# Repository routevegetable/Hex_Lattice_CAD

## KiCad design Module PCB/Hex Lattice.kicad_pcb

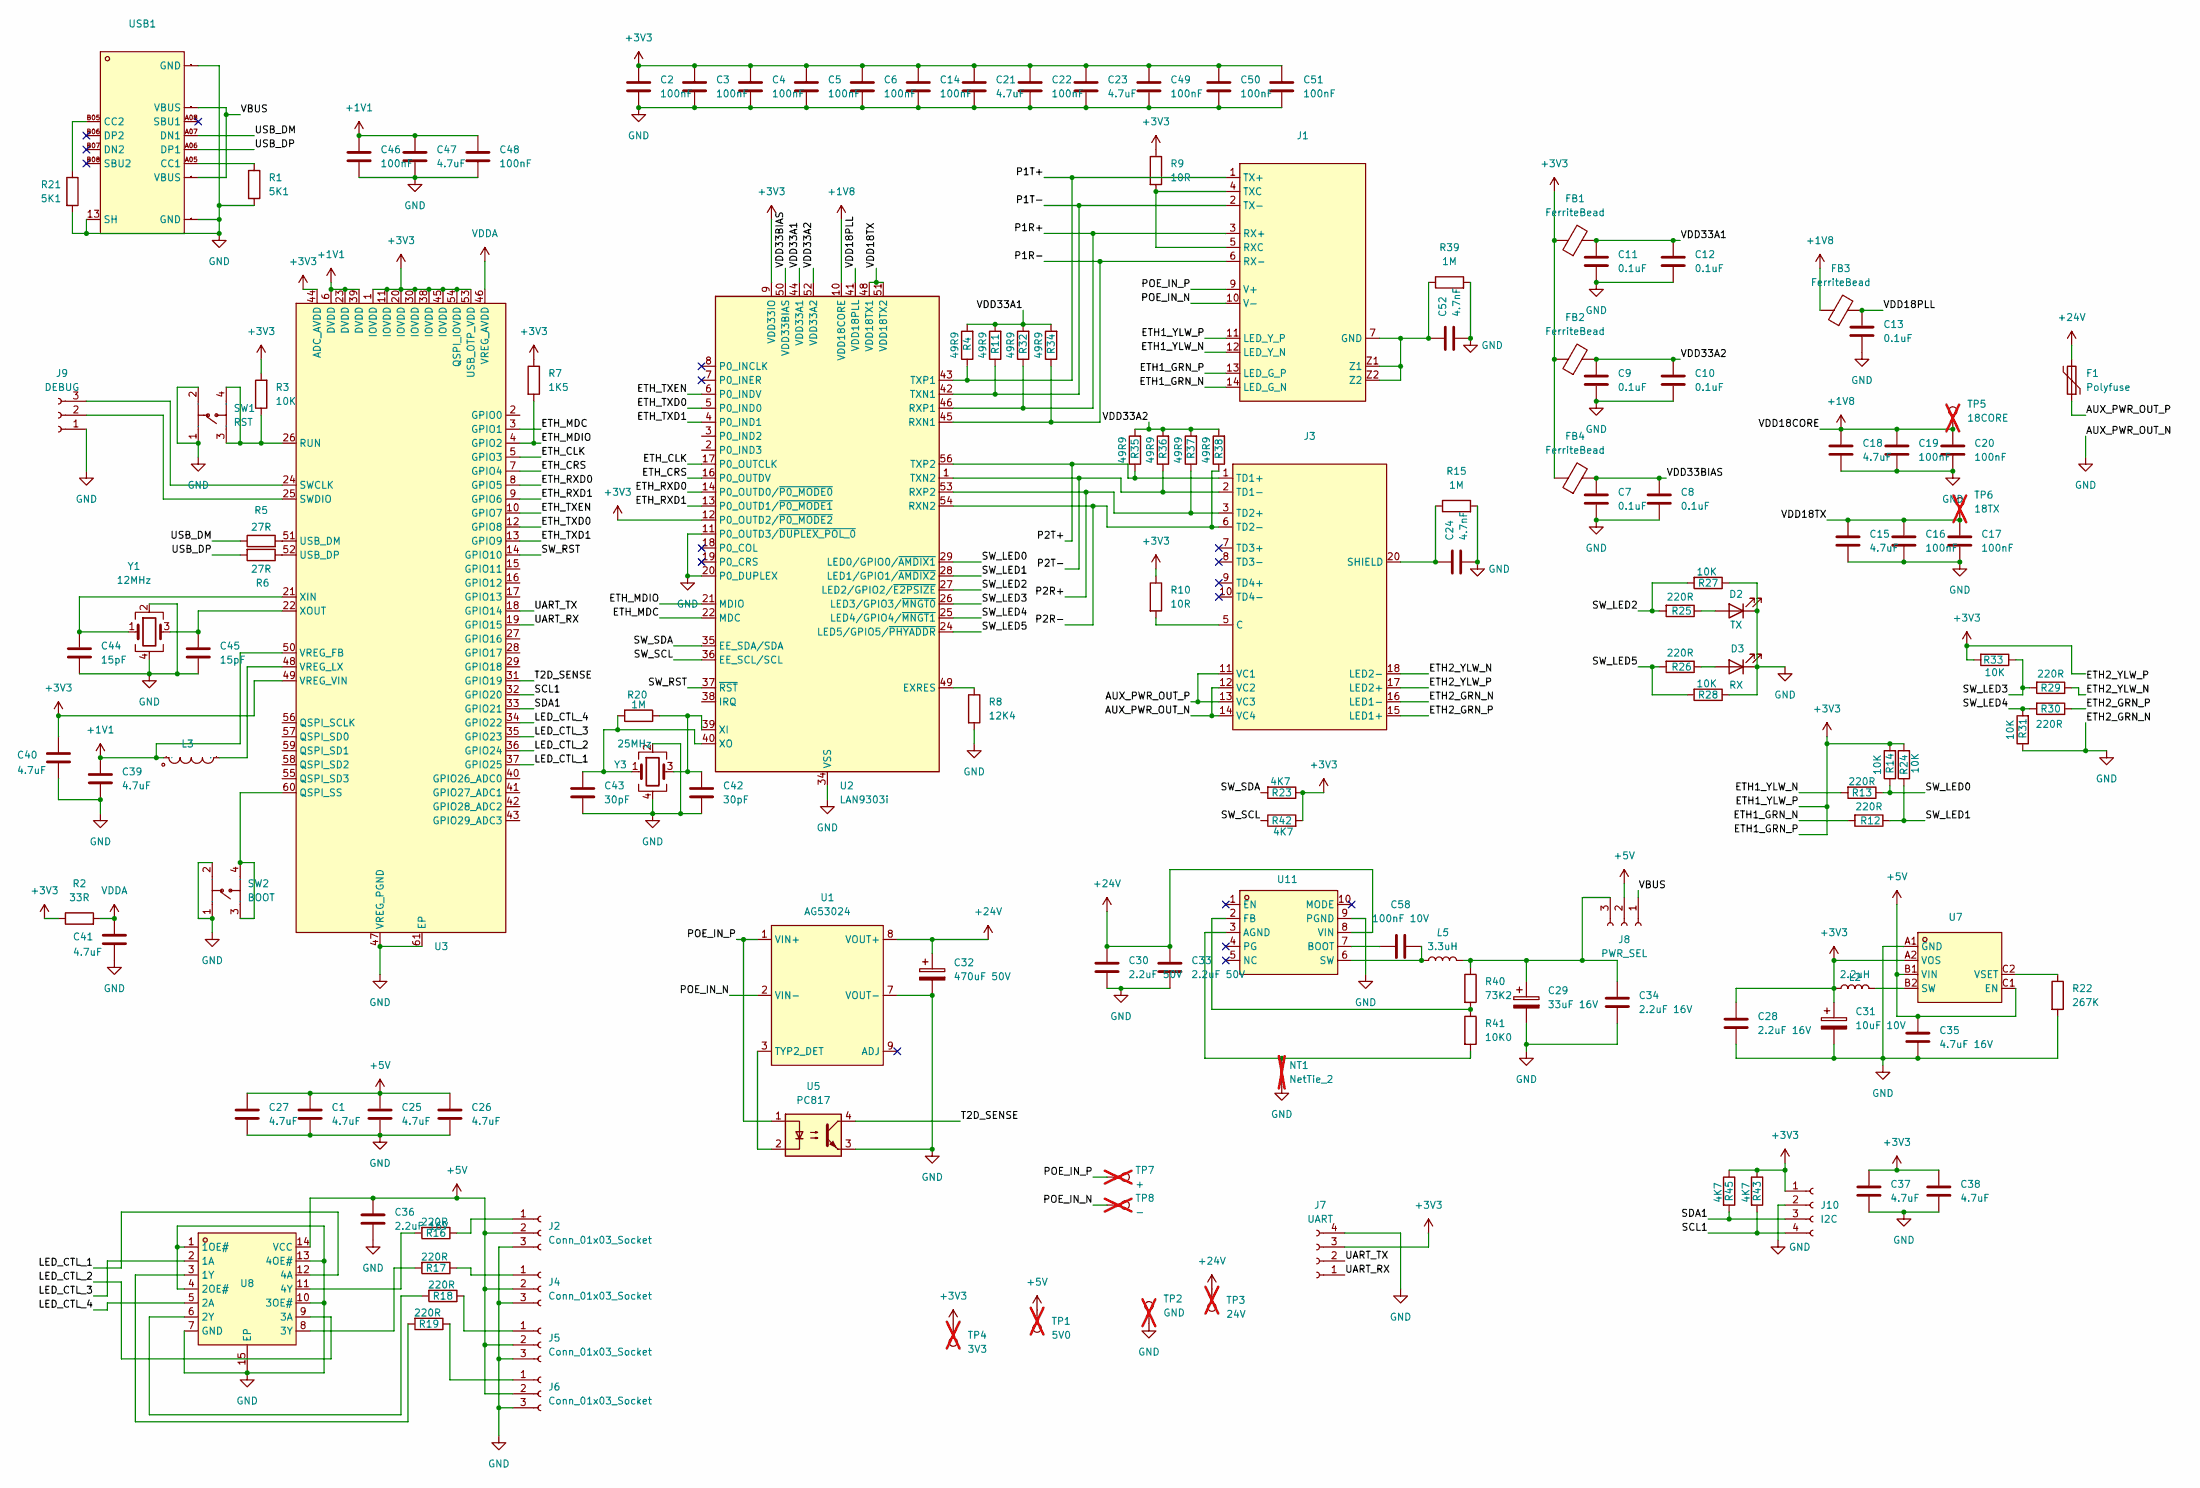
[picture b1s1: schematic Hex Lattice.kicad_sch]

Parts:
C1, C25, C26, C27, C37, C38: 4.7uF; C_0805_2012Metric; LCSC C380343
C2, C3, C4, C5, C6, C14, C16, C17, C19, C20, C22, C46, C48, C49, C50, C51: 100nF; C_0201_0603Metric; LCSC C6119757
C7, C8, C9, C10, C11, C12, C13: 0.1uF; C_0201_0603Metric; LCSC C6119757
C15, C18, C21, C23, C39, C40, C41: 4.7uF; C_0603_1608Metric; LCSC C7419427
C24, C52: 4.7nF; C_1206_3216Metric; LCSC C784438
C28, C34, C36: 2.2uF 16V; C_0805_2012Metric; LCSC C167029
C29: 33uF 16V; CP_Elec_5x5.4; LCSC C970668
C30, C33: 2.2uF 50V; C_0805_2012Metric; LCSC C2903667
C31: 10uF 10V; CP_Elec_4x5.8; LCSC C401860
C32: 470uF 50V; CP_Elec_10x12.5; LCSC C22469994
C35: 4.7uF 16V; C_0805_2012Metric; LCSC C22399641
C42, C43: 30pF; C_0201_0603Metric; LCSC C5142545
C44, C45: 15pF; C_0201_0603Metric; LCSC C22374851
C47: 4.7uF; C_0402_1005Metric; LCSC C33595851
C58: 100nF 10V; C_0201_0603Metric; LCSC C6119757
D2: TX; LED_0402_1005Metric; LCSC C74338
D3: RX; LED_0402_1005Metric; LCSC C74338
F1: Polyfuse; Fuse_Bourns_MF-RG300; LCSC C2680602
FB1, FB2, FB3, FB4: FerriteBead; L_0603_1608Metric; LCSC C3032643
J1: RJ45-TH_ARJP11A-MASA-B-A-EMU2; Manufacturer Part HR861153C; LCSC C19724782
J2, J4, J5, J6: Conn_01x03_Socket; PinHeader_1x03_P2.54mm_Vertical; LCSC C429954
J3: RJ45-TH_DGUK111Q334AB2A2DP057; Manufacturer Part DGUK111Q334AB2A2DP057; LCSC C19725175
J7: UART; CONN-TH_ZH-4A; LCSC C722937
J8: PWR_SEL; PinHeader_1x03_P2.54mm_Vertical; LCSC C429954
J9: DEBUG; PinHeader_1x03_P2.54mm_Vertical; LCSC C2937625
J10: I2C; CONN-SMD_4P-P1.00_ZX-SH1.0-4PLN; LCSC C7430453
L2: 2.2uH; L0806; LCSC C337893
L3: 3.3uH; IND-SMD_L2.0-W1.6_AOTA-B201610S3R3-101-T; Manufacturer Part AOTA-B201610S3R3-101-T; LCSC C42411119
L5: 3.3uH; L_Murata_LQH55DN_5.7x5.0mm; LCSC C48579566
NT1: NetTie_2; NetTie-2_SMD_Pad0.5mm; not fitted
R1, R21: 5K1; R_0402_1005Metric; LCSC C49652827
R2: 33R; R_0201_0603Metric; LCSC C49654095
R3, R14, R24, R27, R28, R31, R33: 10K; R_0201_0603Metric; LCSC C49653975
R4, R11, R32, R34, R35, R36, R37, R38: 49R9; R_0201_0603Metric; LCSC C49653934
R5, R6: 27R; R_0201_0603Metric; LCSC C49654512
R7: 1K5; R_0201_0603Metric; LCSC C49654140
R8: 12K4; R_0402_1005Metric; LCSC C138060
R9, R10: 10R; R_0201_0603Metric; LCSC C49653825
R12, R13, R25, R26, R29, R30: 220R; R_0201_0603Metric; LCSC C49654383
R15, R39: 1M; R_0402_1005Metric; LCSC C49652954
R16, R17, R18, R19: 220R; R_0402_1005Metric; LCSC C49653096
R20: 1M; R_0201_0603Metric; LCSC C49654212
R22: 267K; R_0402_1005Metric; LCSC C49254102
R23, R42, R43, R45: 4K7; R_0201_0603Metric; LCSC C49654757
R40: 73K2; R_0402_1005Metric; LCSC C50669973
R41: 10K0; R_0402_1005Metric; LCSC C52677569
SW1: RST; SW-SMD_4P-L5.2-W5.2-P3.70-LS6.4; Manufacturer Part TS1187A16015; LCSC C22375382
SW2: BOOT; SW-SMD_4P-L5.2-W5.2-P3.70-LS6.4; Manufacturer Part TS1187A16015; LCSC C22375382
TP1: 5V0; TestPoint_Pad_D3.0mm; not fitted
TP2: GND; TestPoint_Pad_D3.0mm; not fitted
TP3: 24V; TestPoint_Pad_D3.0mm; not fitted
TP4: 3V3; TestPoint_Pad_D3.0mm; not fitted
TP5: 18CORE; TestPoint_Pad_D2.0mm; not fitted
TP6: 18TX; TestPoint_Pad_D2.0mm; not fitted
TP7: +; TestPoint_Pad_D3.0mm; not fitted
TP8: -; TestPoint_Pad_D3.0mm; not fitted
U1: AG53024; AG53000
U2: LAN9303i; QFN-56-1EP_8x8mm_P0.5mm_EP5.9x5.9mm_ThermalVias; LCSC C633501
U3: QFN-60_L7.0-W7.0-P0.40-TL-EP3.4; Manufacturer Part RP2354A; LCSC C41378174
U5: PC817; DIP-4_W7.62mm; LCSC C52092020
U7: DSBGA-6_L1.4-W1.0-R2-C3-P0.40-BL; Manufacturer Part TPS62840YBGR; LCSC C2071139
U8: DHVQFN-14_L3.0-W2.5-P0.50-BL-EP; Manufacturer Part 74AHCT125BQ,115; LCSC C554499
U11: VQFN-HR-10_L3.0-W3.0_RPA; Manufacturer Part TPS56637RPAR; LCSC C841386
USB1: USB-C-TH_MC-110LD-L137; Manufacturer Part MC-110LDS-L150; LCSC C22374560
Y1: 12MHz; Crystal_SMD_3225-4Pin_3.2x2.5mm; LCSC C5182759
Y3: 25MHz; CRYSTAL-SMD_4P-L1.6-W1.2-BL; LCSC C51289919

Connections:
+1V1: C39.1, C46.1, C47.1, C48.1, L3.2, U3.6 (DVDD), U3.23 (DVDD), U3.39 (DVDD), U3.50 (VREG_FB)
+1V8: C18.1, C19.1, C20.1, FB3.1, TP5.1, U2.10 (VDD18CORE), U2.31 (VDD18CORE)
+3V3: C2.1, C3.1, C4.1, C5.1, C6.1, C14.1, C21.1, C22.1, C23.1, C28.2, C31.1, C37.1, C38.1, C40.1, C49.1, C50.1, C51.1, FB1.1, FB2.1, FB4.1, J1.11 (LED_Y_P), J1.13 (LED_G_P), J7.3, J10.1, L2.1, R2.1, R3.2, R7.1, R9.1, R10.1, R14.2, R23.1, R24.2, R33.2, R42.2, R43.1, R45.1, TP4.1, U2.9 (VDD33IO), U2.12 (P0_OUTD2/~P0_MODE2), U2.15 (VDD33IO), U2.23 (VDD33IO), U2.30 (VDD33IO), U2.32 (VDD33IO), U2.33 (VDD33IO), U3.1 (IOVDD), U3.11 (IOVDD), U3.20 (IOVDD), U3.30 (IOVDD), U3.38 (IOVDD), U3.44 (ADC_AVDD), U3.45 (IOVDD), U3.49 (VREG_VIN), U3.53 (USB_OTP_VDD), U3.54 (QSPI_IOVDD), U7.A2 (VOS)
+5V: C1.1, C25.1, C26.1, C27.1, C35.1, C36.2, J2.2, J4.2, J5.2, J6.2, J8.2, TP1.1, U7.B1 (VIN), U7.C1 (EN), U8.14 (VCC)
+24V: C30.2, C32.1, C33.2, F1.2, TP3.1, U1.8 (VOUT+), U11.8 (VIN)
/AUX_PWR_OUT_P: F1.1, J3.11 (VC1), J3.13 (VC3)
/ETH1_GRN_N: J1.14 (LED_G_N), R12.2
/ETH1_YLW_N: J1.12 (LED_Y_N), R13.2
/ETH2_GRN_P: J3.15 (LED1+), R30.1
/ETH2_YLW_N: J3.18 (LED2-), R29.1
/ETH2_YLW_P: J3.17 (LED2+)
/ETH_CLK: U2.17 (P0_OUTCLK), U3.5 (GPIO3)
/ETH_CRS: U2.16 (P0_OUTDV), U3.7 (GPIO4)
/ETH_MDC: U2.22 (MDC), U3.3 (GPIO1)
/ETH_MDIO: R7.2, U2.21 (MDIO), U3.4 (GPIO2)
/ETH_RXD0: U2.14 (P0_OUTD0/~P0_MODE0), U3.8 (GPIO5)
/ETH_RXD1: U2.13 (P0_OUTD1/~P0_MODE1), U3.9 (GPIO6)
/ETH_TXD0: U2.5 (P0_IND0), U3.12 (GPIO8)
/ETH_TXD1: U2.4 (P0_IND1), U3.13 (GPIO9)
/ETH_TXEN: U2.6 (P0_INDV), U3.10 (GPIO7)
/LED_CTL_1: U3.37 (GPIO25), U8.12 (4A)
/LED_CTL_2: U3.36 (GPIO24), U8.9 (3A)
/LED_CTL_3: U3.35 (GPIO23), U8.2 (1A)
/LED_CTL_4: U3.34 (GPIO22), U8.5 (2A)
/P1R+: J1.3 (RX+), R32.1, U2.46 (RXP1)
/P1R-: J1.6 (RX-), R34.1, U2.45 (RXN1)
/P1T+: J1.1 (TX+), R4.1, U2.43 (TXP1)
/P1T-: J1.2 (TX-), R11.1, U2.42 (TXN1)
/P2R+: J3.3 (TD2+), R37.1, U2.53 (RXP2)
/P2R-: J3.6 (TD2-), R38.1, U2.54 (RXN2)
/P2T+: J3.1 (TD1+), R35.1, U2.56 (TXP2)
/P2T-: J3.2 (TD1-), R36.1, U2.1 (TXN2)
/POE_IN_N: J1.10 (V-), TP8.1, U1.2 (VIN-)
/POE_IN_P: J1.9 (V+), TP7.1, U1.1 (VIN+), U5.1
/SCL1: J10.4, R43.2, U3.32 (GPIO20)
/SDA1: J10.3, R45.2, U3.33 (GPIO21)
/SW_LED0: R13.1, R14.1, U2.29 (LED0/GPIO0/~AMDIX1)
/SW_LED1: R12.1, R24.1, U2.28 (LED1/GPIO1/~AMDIX2)
/SW_LED2: R25.2, R27.2, U2.27 (LED2/GPIO2/~E2PSIZE)
/SW_LED3: R29.2, R33.1, U2.26 (LED3/GPIO3/~MNGT0)
/SW_LED4: R30.2, R31.2, U2.25 (LED4/GPIO4/~MNGT1)
/SW_LED5: R26.2, R28.2, U2.24 (LED5/GPIO5/~PHYADDR)
/SW_RST: U2.37 (~RST), U3.14 (GPIO10)
/SW_SCL: R42.1, U2.36 (EE_SCL/SCL)
/SW_SDA: R23.2, U2.35 (EE_SDA/SDA)
/T2D_SENSE: U3.31 (GPIO19), U5.4
/UART_RX: J7.1, U3.19 (GPIO15)
/UART_TX: J7.2, U3.18 (GPIO14)
/USB_DM: R5.1, USB1.A07 (DN1)
/USB_DP: R6.2, USB1.A06 (DP1)
/VBUS: J8.1, USB1.A04 (VBUS), USB1.A09 (VBUS)
/VDD18PLL: C13.1, FB3.2, U2.41 (VDD18PLL)
/VDD18TX: C15.1, C16.1, C17.1, TP6.1, U2.48 (VDD18TX1), U2.51 (VDD18TX2)
/VDD33A1: C11.1, C12.1, FB1.2, R4.2, R11.2, R32.2, R34.2, U2.44 (VDD33A1), U2.47 (VDD33A1)
/VDD33A2: C9.1, C10.1, FB2.2, R35.2, R36.2, R37.2, R38.2, U2.52 (VDD33A2), U2.55 (VDD33A2)
/VDD33BIAS: C7.1, C8.1, FB4.2, U2.50 (VDD33BIAS)
GND: C1.2, C2.2, C3.2, C4.2, C5.2, C6.2, C7.2, C8.2, C9.2, C10.2, C11.2, C12.2, C13.2, C14.2, C15.2, C16.2, C17.2, C18.2, C19.2, C20.2, C21.2, C22.2, C23.2, C24.2, C25.2, C26.2, C27.2, C28.1, C29.2, C30.1, C31.2, C32.2, C33.1, C34.1, C35.2, C36.1, C37.2, C38.2, C39.2, C40.2, C41.2, C42.2, C43.2, C44.2, C45.2, C46.2, C47.2, C48.2, C49.2, C50.2, C51.2, C52.2, D2.1 (K), D3.1 (K), J2.3, J3.12 (VC2), J3.14 (VC4), J3.16 (LED1-), J4.3, J5.3, J6.3, J7.4, J9.1, J10.2, NT1.1, R1.2, R8.2, R15.2, R21.2, R22.2, R27.1, R28.1, R31.1, R39.2, SW1.1, SW1.2, SW2.1, SW2.2, TP2.1, U1.7 (VOUT-), U1.10 (VOUT-), U2.11 (P0_OUTD3/~DUPLEX_POL_0), U2.20 (P0_DUPLEX), U2.34 (VSS), U2.57 (VSS), U3.47 (VREG_PGND), U3.61 (EP), U5.3, U7.A1 (GND), U8.1 (1OE#), U8.4 (2OE#), U8.7 (GND), U8.10 (3OE#), U8.13 (4OE#), U8.15 (EP), U11.9 (PGND), USB1.13 (SH), USB1.A01 (GND), USB1.A12 (GND), Y1.2, Y1.4, Y3.2, Y3.4
unnamed: C24.1, J3.19 (SHIELD), J3.20 (SHIELD), R15.1
unnamed: D2.2 (A), R25.1
unnamed: D3.2 (A), R26.1
unnamed: C52.1, J1.7 (GND), J1.Z1, J1.Z2, R39.1
unnamed: J1.4 (TXC), J1.5 (RXC), R9.2
unnamed: J2.1, R16.1
unnamed: J3.4 (C), J3.5 (C), R10.2
unnamed: J4.1, R17.1
unnamed: J5.1, R18.1
unnamed: J6.1, R19.1
unnamed: C29.1, C34.2, J8.3, L5.2, R40.1
unnamed: J9.2, U3.25 (SWDIO)
unnamed: J9.3, U3.24 (SWCLK)
unnamed: U1.3 (TYP2_DET), U5.2
unnamed: R8.1, U2.49 (EXRES)
unnamed: C42.1, R20.1, U2.39 (XI), Y3.3
unnamed: C43.1, R20.2, U2.40 (XO), Y3.1
unnamed: SW2.3, SW2.4, U3.60 (QSPI_SS)
unnamed: R3.1, SW1.3, SW1.4, U3.26 (RUN)
unnamed: R5.2, U3.51 (USB_DM)
unnamed: R6.1, U3.52 (USB_DP)
unnamed: L3.1, U3.48 (VREG_LX)
unnamed: C44.1, U3.21 (XIN), Y1.1
unnamed: C45.1, U3.22 (XOUT), Y1.3
unnamed: L2.2, U7.B2 (SW)
unnamed: R22.1, U7.C2 (VSET)
unnamed: R19.2, U8.3 (1Y)
unnamed: R18.2, U8.6 (2Y)
unnamed: R17.2, U8.8 (3Y)
unnamed: R16.2, U8.11 (4Y)
unnamed: NT1.2, R41.2, U11.3 (AGND)
unnamed: C58.1, U11.7 (BOOT)
unnamed: R40.2, R41.1, U11.2 (FB)
unnamed: C58.2, L5.1, U11.6 (SW)
unnamed: R1.1, USB1.A05 (CC1)
unnamed: R21.1, USB1.B05 (CC2)
VDDA: C41.1, R2.2, U3.46 (VREG_AVDD)

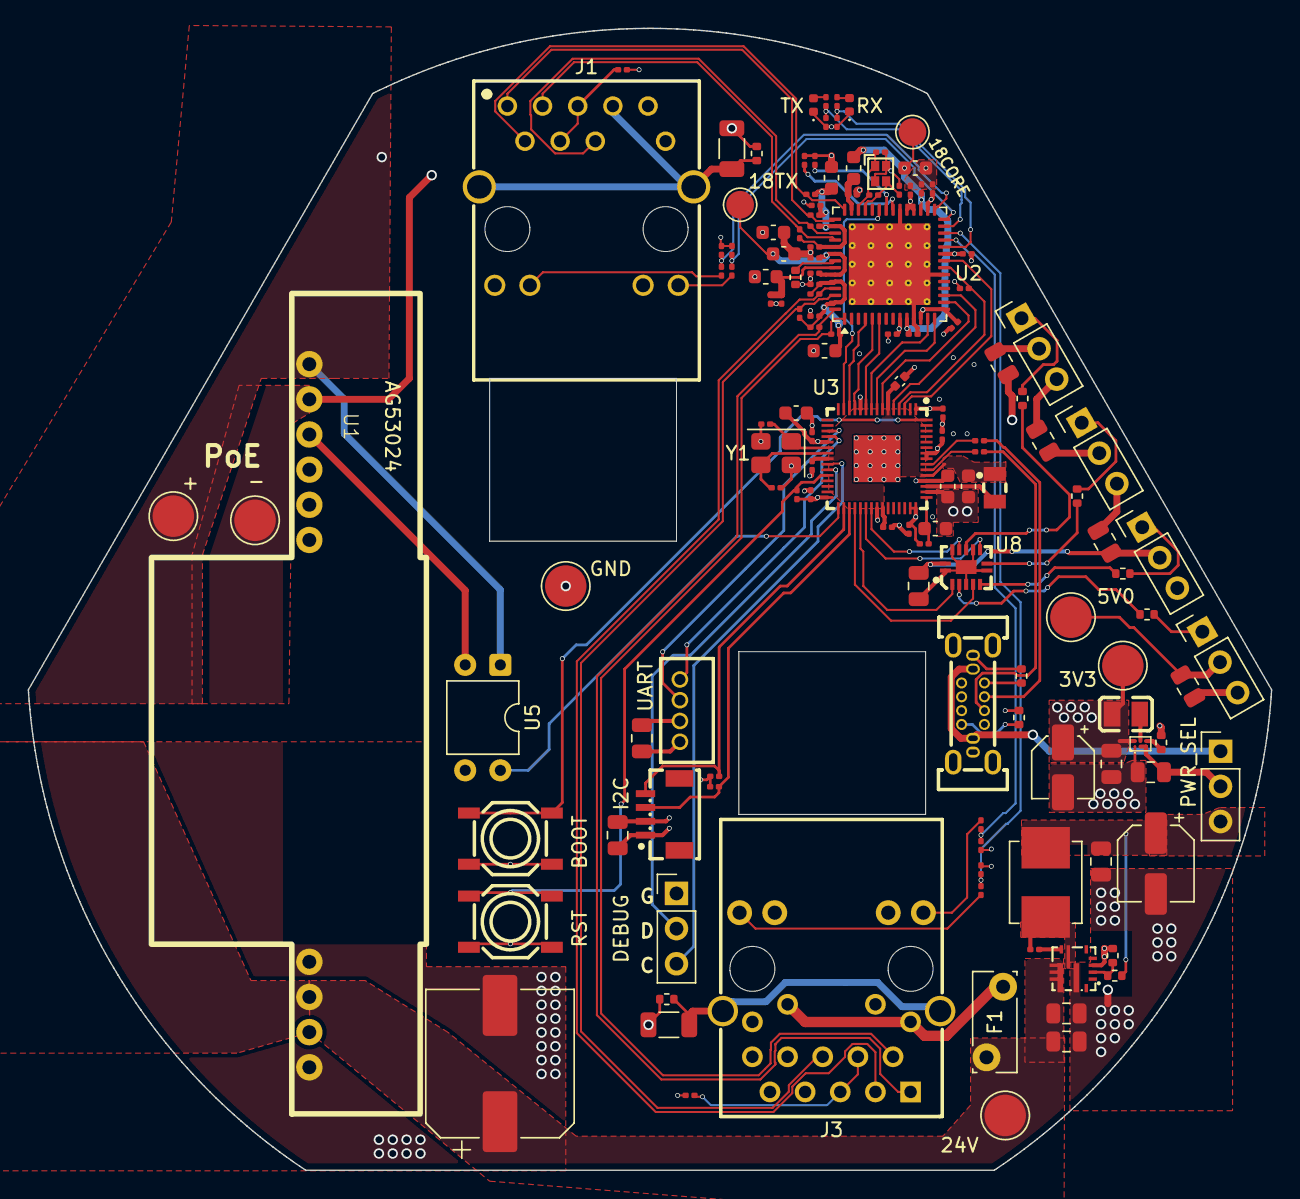
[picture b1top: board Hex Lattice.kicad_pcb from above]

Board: 4 copper layers, 89.8 x 82.5 mm, 138 parts (0 on the bottom side), 93 nets.

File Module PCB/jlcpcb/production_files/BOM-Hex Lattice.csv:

Comment,Designator,Footprint,LCSC,Quantity
0.1uF,"C10,C11,C12,C13,C7,C8,C9",C_0201_0603Metric,C6119757,7
100nF,"C14,C16,C17,C19,C2,C20,C22,C3,C4,C46,C48,C49,C5,C50,C51,C6",C_0201_0603Metric,C6119757,16
100nF 10V,C58,C_0201_0603Metric,C6119757,1
10K,"R14,R24,R27,R28,R3,R31,R33",R_0201_0603Metric,C49653975,7
10K0,R41,R_0402_1005Metric,C52677569,1
10R,"R10,R9",R_0201_0603Metric,C49653825,2
10uF 10V,C31,CP_Elec_4x5.8,C401860,1
12K4,R8,R_0402_1005Metric,C138060,1
12MHz,Y1,Crystal_SMD_3225-4Pin_3.2x2.5mm,C5182759,1
15pF,"C44,C45",C_0201_0603Metric,C22374851,2
1K5,R7,R_0201_0603Metric,C49654140,1
1M,"R15,R39",R_0402_1005Metric,C49652954,2
1M,R20,R_0201_0603Metric,C49654212,1
2.2uF 16V,"C28,C34,C36",C_0805_2012Metric,C167029,3
2.2uF 50V,"C30,C33",C_0805_2012Metric,C2903667,2
2.2uH,L2,L0806,C337893,1
220R,"R16,R17,R18,R19",R_0402_1005Metric,C49653096,4
220R,"R12,R13,R25,R26,R29,R30",R_0201_0603Metric,C49654383,6
25MHz,Y3,CRYSTAL-SMD_4P-L1.6-W1.2-BL,C51289919,1
267K,R22,R_0402_1005Metric,C49254102,1
27R,"R5,R6",R_0201_0603Metric,C49654512,2
3.3uH,L3,IND-SMD_L2.0-W1.6_AOTA-B201610S3R3-101-T,C42411119,1
3.3uH,L5,L_Murata_LQH55DN_5.7x5.0mm,C48579566,1
30pF,"C42,C43",C_0201_0603Metric,C5142545,2
33R,R2,R_0201_0603Metric,C49654095,1
33uF 16V,C29,CP_Elec_5x5.4,C970668,1
4.7nF,"C24,C52",C_1206_3216Metric,C784438,2
4.7uF,C47,C_0402_1005Metric,C33595851,1
4.7uF,"C1,C25,C26,C27,C37,C38",C_0805_2012Metric,C380343,6
4.7uF,"C15,C18,C21,C23,C39,C40,C41",C_0603_1608Metric,C7419427,7
4.7uF 16V,C35,C_0805_2012Metric,C22399641,1
470uF 50V,C32,CP_Elec_10x12.5,C22469994,1
49R9,"R11,R32,R34,R35,R36,R37,R38,R4",R_0201_0603Metric,C49653934,8
4K7,"R23,R42,R43,R45",R_0201_0603Metric,C49654757,4
5K1,"R1,R21",R_0402_1005Metric,C49652827,2
73K2,R40,R_0402_1005Metric,C50669973,1
BOOT,SW2,SW-SMD_4P-L5.2-W5.2-P3.70-LS6.4,C22375382,1
Conn_01x03_Socket,"J2,J4,J5,J6",PinHeader_1x03_P2.54mm_Vertical,C429954,4
DEBUG,J9,PinHeader_1x03_P2.54mm_Vertical,C2937625,1
FerriteBead,"FB1,FB2,FB3,FB4",L_0603_1608Metric,C3032643,4
I2C,J10,CONN-SMD_4P-P1.00_ZX-SH1.0-4PLN,C5447903,1
LAN9303i,U2,QFN-56-1EP_8x8mm_P0.5mm_EP5.9x5.9mm_ThermalVias,C633501,1
PC817,U5,DIP-4_W7.62mm,C52092020,1
PWR_SEL,J8,PinHeader_1x03_P2.54mm_Vertical,C429954,1
Polyfuse,F1,Fuse_Bourns_MF-RG300,C2680600,1
RST,SW1,SW-SMD_4P-L5.2-W5.2-P3.70-LS6.4,C22375382,1
RX,D3,LED_0402_1005Metric,C74338,1
TX,D2,LED_0402_1005Metric,C74338,1
UART,J7,CONN-TH_ZH-4A,C722937,1
~,J1,RJ45-TH_ARJP11A-MASA-B-A-EMU2,C19724782,1
~,J3,RJ45-TH_DGUK111Q334AB2A2DP057,C19725175,1
~,U7,DSBGA-6_L1.4-W1.0-R2-C3-P0.40-BL,C2071139,1
~,USB1,USB-C-TH_MC-110LD-L137,C22374560,1
~,U3,QFN-60_L7.0-W7.0-P0.40-TL-EP3.4,C41378174,1
~,U8,DHVQFN-14_L3.0-W2.5-P0.50-BL-EP,C554499,1
~,U11,VQFN-HR-10_L3.0-W3.0_RPA,C841386,1
